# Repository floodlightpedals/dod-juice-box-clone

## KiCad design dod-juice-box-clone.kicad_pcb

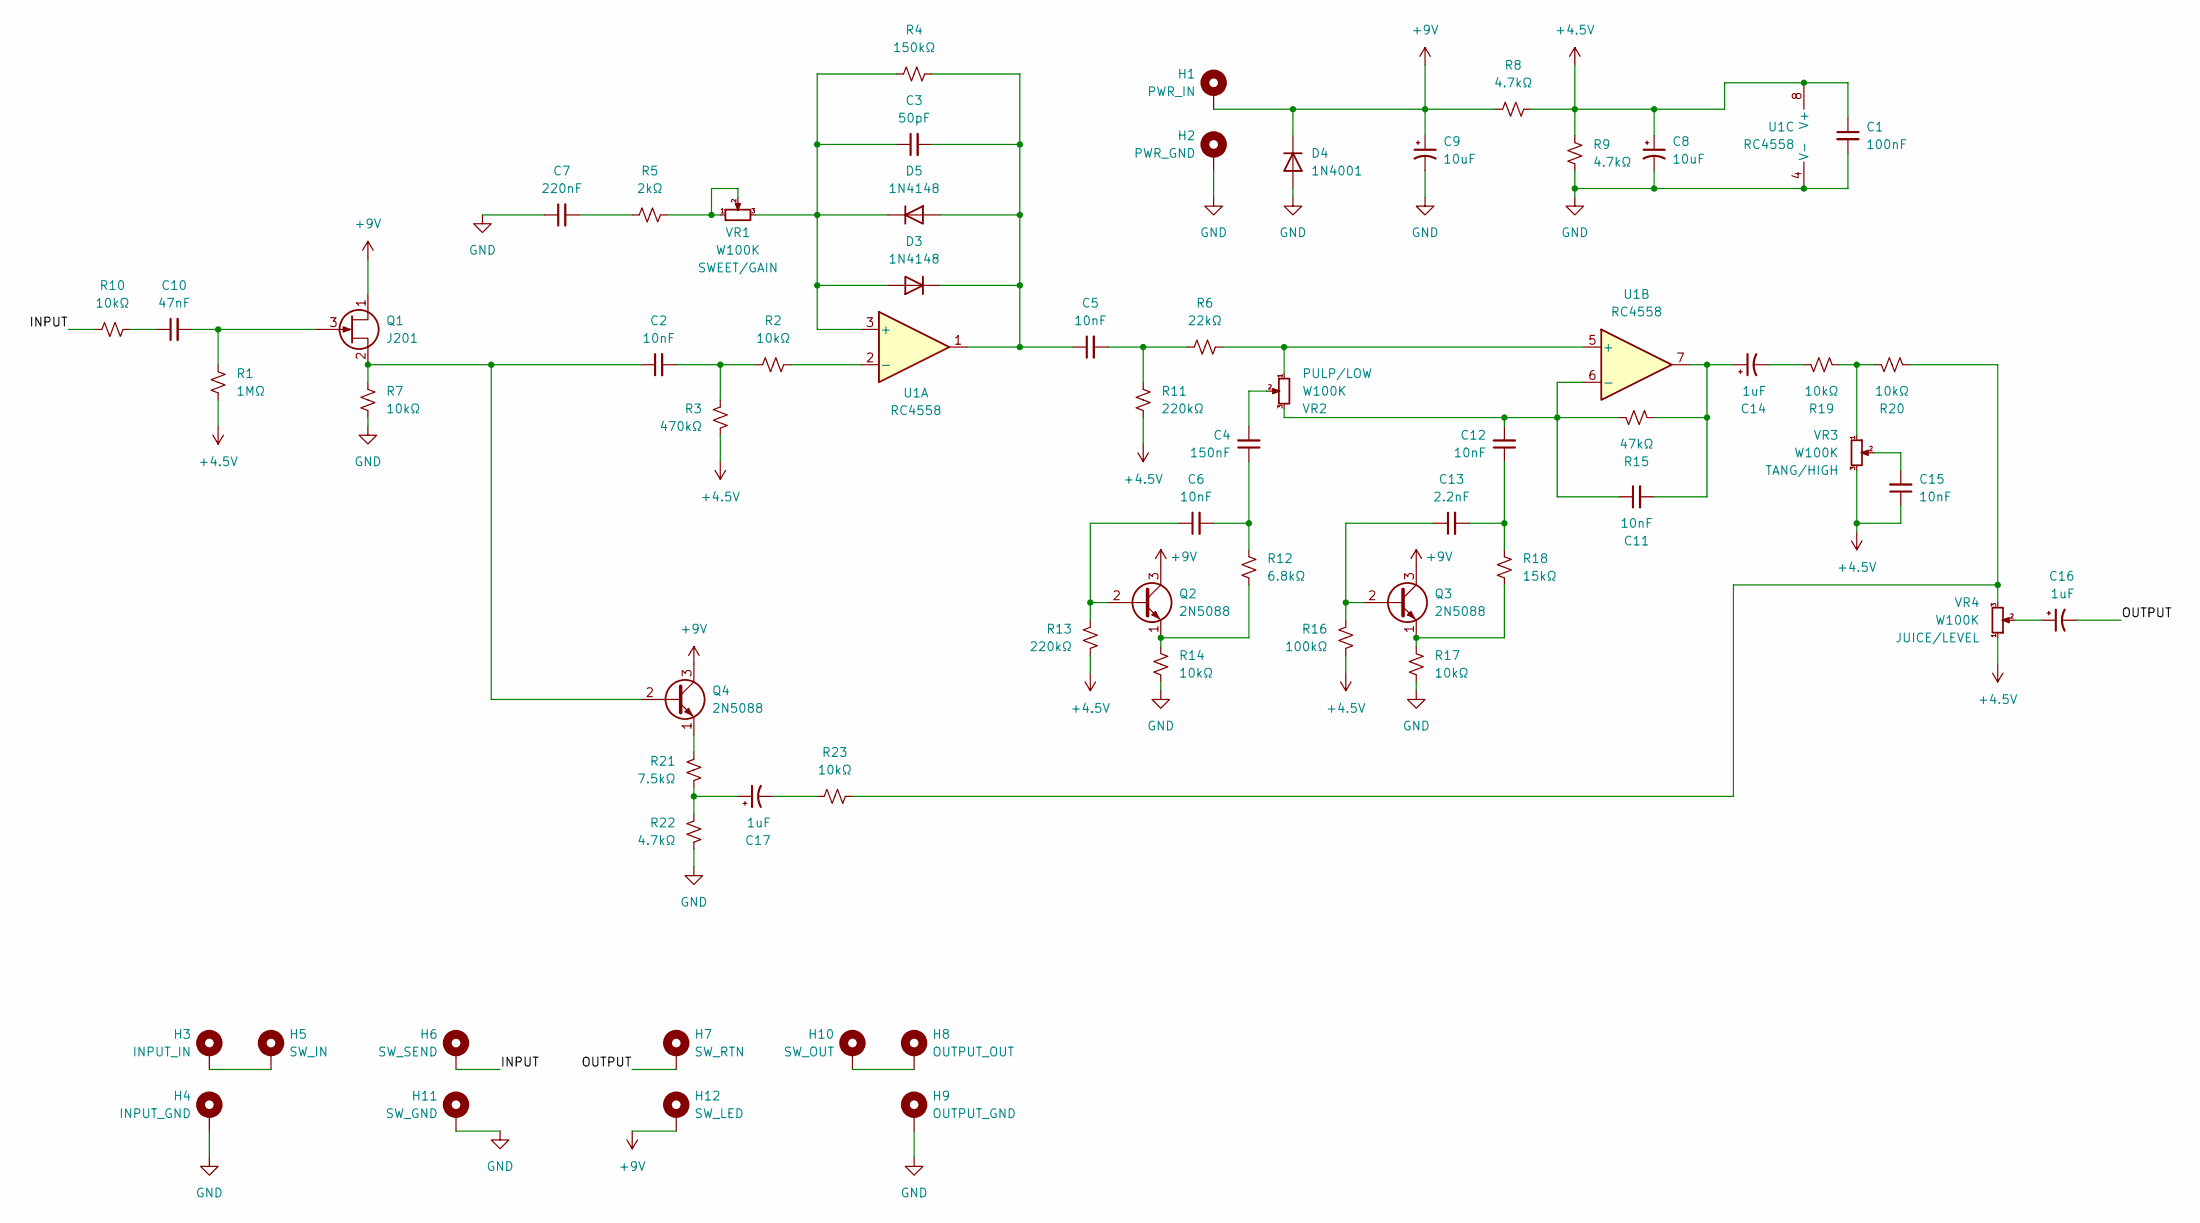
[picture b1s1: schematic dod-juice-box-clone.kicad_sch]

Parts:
C1: 100nF; C_Rect_L7.2mm_W2.5mm_P5.00mm_FKS2_FKP2_MKS2_MKP2
C2, C5, C6, C11, C12, C15: 10nF; C_Rect_L7.2mm_W2.5mm_P5.00mm_FKS2_FKP2_MKS2_MKP2
C3: 50pF; C_Disc_D3.8mm_W2.6mm_P2.50mm
C4: 150nF; C_Rect_L7.2mm_W2.5mm_P5.00mm_FKS2_FKP2_MKS2_MKP2
C7: 220nF; C_Rect_L7.2mm_W2.5mm_P5.00mm_FKS2_FKP2_MKS2_MKP2
C8, C9: 10uF; CP_Radial_D6.3mm_P2.50mm
C10: 47nF; C_Rect_L7.2mm_W2.5mm_P5.00mm_FKS2_FKP2_MKS2_MKP2
C13: 2.2nF; C_Rect_L7.2mm_W2.5mm_P5.00mm_FKS2_FKP2_MKS2_MKP2
C14, C16, C17: 1uF; CP_Radial_D6.3mm_P2.50mm
D3, D5: 1N4148; D_DO-35_SOD27_P7.62mm_Horizontal
D4: 1N4001; D_DO-41_SOD81_P10.16mm_Horizontal
H1: PWR_IN; MountingHole_2.2mm_M2_DIN965_Pad_TopBottom
H2: PWR_GND; MountingHole_2.2mm_M2_DIN965_Pad_TopBottom
H3: INPUT_IN; MountingHole_2.2mm_M2_DIN965_Pad_TopBottom
H4: INPUT_GND; MountingHole_2.2mm_M2_DIN965_Pad_TopBottom
H5: SW_IN; MountingHole_2.2mm_M2_DIN965_Pad_TopBottom
H6: SW_SEND; MountingHole_2.2mm_M2_DIN965_Pad_TopBottom
H7: SW_RTN; MountingHole_2.2mm_M2_DIN965_Pad_TopBottom
H8: OUTPUT_OUT; MountingHole_2.2mm_M2_DIN965_Pad_TopBottom
H9: OUTPUT_GND; MountingHole_2.2mm_M2_DIN965_Pad_TopBottom
H10: SW_OUT; MountingHole_2.2mm_M2_DIN965_Pad_TopBottom
H11: SW_GND; MountingHole_2.2mm_M2_DIN965_Pad_TopBottom
H12: SW_LED; MountingHole_2.2mm_M2_DIN965_Pad_TopBottom
Q1: J201; TO-92_Inline
Q2, Q3, Q4: 2N5088; TO-92_Inline
R1: 1MΩ; R_Axial_DIN0207_L6.3mm_D2.5mm_P7.62mm_Horizontal
R2, R7, R10, R14, R17, R19, R20, R23: 10kΩ; R_Axial_DIN0207_L6.3mm_D2.5mm_P7.62mm_Horizontal
R3: 470kΩ; R_Axial_DIN0207_L6.3mm_D2.5mm_P7.62mm_Horizontal
R4: 150kΩ; R_Axial_DIN0207_L6.3mm_D2.5mm_P7.62mm_Horizontal
R5: 2kΩ; R_Axial_DIN0207_L6.3mm_D2.5mm_P7.62mm_Horizontal
R6: 22kΩ; R_Axial_DIN0207_L6.3mm_D2.5mm_P7.62mm_Horizontal
R8, R9, R22: 4.7kΩ; R_Axial_DIN0207_L6.3mm_D2.5mm_P7.62mm_Horizontal
R11, R13: 220kΩ; R_Axial_DIN0207_L6.3mm_D2.5mm_P7.62mm_Horizontal
R12: 6.8kΩ; R_Axial_DIN0207_L6.3mm_D2.5mm_P7.62mm_Horizontal
R15: 47kΩ; R_Axial_DIN0207_L6.3mm_D2.5mm_P7.62mm_Horizontal
R16: 100kΩ; R_Axial_DIN0207_L6.3mm_D2.5mm_P7.62mm_Horizontal
R18: 15kΩ; R_Axial_DIN0207_L6.3mm_D2.5mm_P7.62mm_Horizontal
R21: 7.5kΩ; R_Axial_DIN0207_L6.3mm_D2.5mm_P7.62mm_Horizontal
U1: RC4558; DIP-8_W7.62mm
VR1, VR2, VR3, VR4: W100K; Alpha_RV16AF-41

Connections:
+4.5V: C1.1, C8.1, C15.1, R1.2, R3.2, R8.2, R9.2, R11.1, R13.1, R16.1, U1.8 (V+), VR3.3, VR4.1; also elsewhere on the board
+9V: C9.1, D4.1 (K), H1.1, H12.1, Q1.1 (D), Q2.3 (C), Q3.3 (C), Q4.3 (C), R8.1
/INPUT: H6.1, R10.1
/OUTPUT: C16.2, H7.1
GND: C1.2, C7.1, C8.2, C9.2, D4.2 (A), H2.1, H4.1, H9.1, H11.1, R7.2, R9.1, R14.1, R17.1, R22.1, U1.4 (V-)
unnamed: C2.2, R2.1, R3.1
unnamed: C4.1, C6.2, R12.2
unnamed 7: C4.2, VR2.2; also elsewhere on the board
unnamed: C5.2, R6.1, R11.2
unnamed: C7.2, R5.1
unnamed: C10.1, R10.2
unnamed: C11.2, C14.1, R15.2, U1.7
unnamed: C12.1, C13.2, R18.2
unnamed: C14.2, R19.1
unnamed 14: C15.2, VR3.2; also elsewhere on the board
unnamed 15: C16.1, VR4.2; also elsewhere on the board
unnamed: C17.1, R21.1, R22.2
unnamed: C17.2, R23.1
unnamed 18: C3.1, D3.2 (A), D5.1 (K), R4.1, U1.3 (+), VR1.3; also elsewhere on the board
unnamed: C3.2, C5.1, D3.1 (K), D5.2 (A), R4.2, U1.1
unnamed: H3.1, H5.1
unnamed: H8.1, H10.1
unnamed: C10.2, Q1.3 (G), R1.1
unnamed: C2.1, Q1.2 (S), Q4.2 (B), R7.1
unnamed: C6.1, Q2.2 (B), R13.2
unnamed: Q2.1 (E), R12.1, R14.2
unnamed: C13.1, Q3.2 (B), R16.2
unnamed: Q3.1 (E), R17.2, R18.1
unnamed: Q4.1 (E), R21.2
unnamed 29: R5.2, VR1.1, VR1.2; also elsewhere on the board
unnamed 30: R19.2, R20.1, VR3.1; also elsewhere on the board
unnamed 31: R20.2, R23.2, VR4.3; also elsewhere on the board
unnamed: R2.2, U1.2 (-)
unnamed 33: R6.2, U1.5 (+), VR2.1; also elsewhere on the board
unnamed 34: C11.1, C12.2, R15.1, U1.6 (-), VR2.3; also elsewhere on the board

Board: 2 copper layers, 64 parts (4 on the bottom side), 35 nets, no tracks yet.

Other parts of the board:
RV1, RV2, RV3, RV4: W100K; Potentiometer_Omeg_PC16BU_Vertical

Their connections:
+4.5V: RV3.3, RV4.1; also elsewhere on the board
unnamed 7: RV2.2; also elsewhere on the board
unnamed 14: RV3.2; also elsewhere on the board
unnamed 15: RV4.2; also elsewhere on the board
unnamed 18: RV1.3; also elsewhere on the board
unnamed 29: RV1.1, RV1.2; also elsewhere on the board
unnamed 30: RV3.1; also elsewhere on the board
unnamed 31: RV4.3; also elsewhere on the board
unnamed 33: RV2.1; also elsewhere on the board
unnamed 34: RV2.3; also elsewhere on the board
